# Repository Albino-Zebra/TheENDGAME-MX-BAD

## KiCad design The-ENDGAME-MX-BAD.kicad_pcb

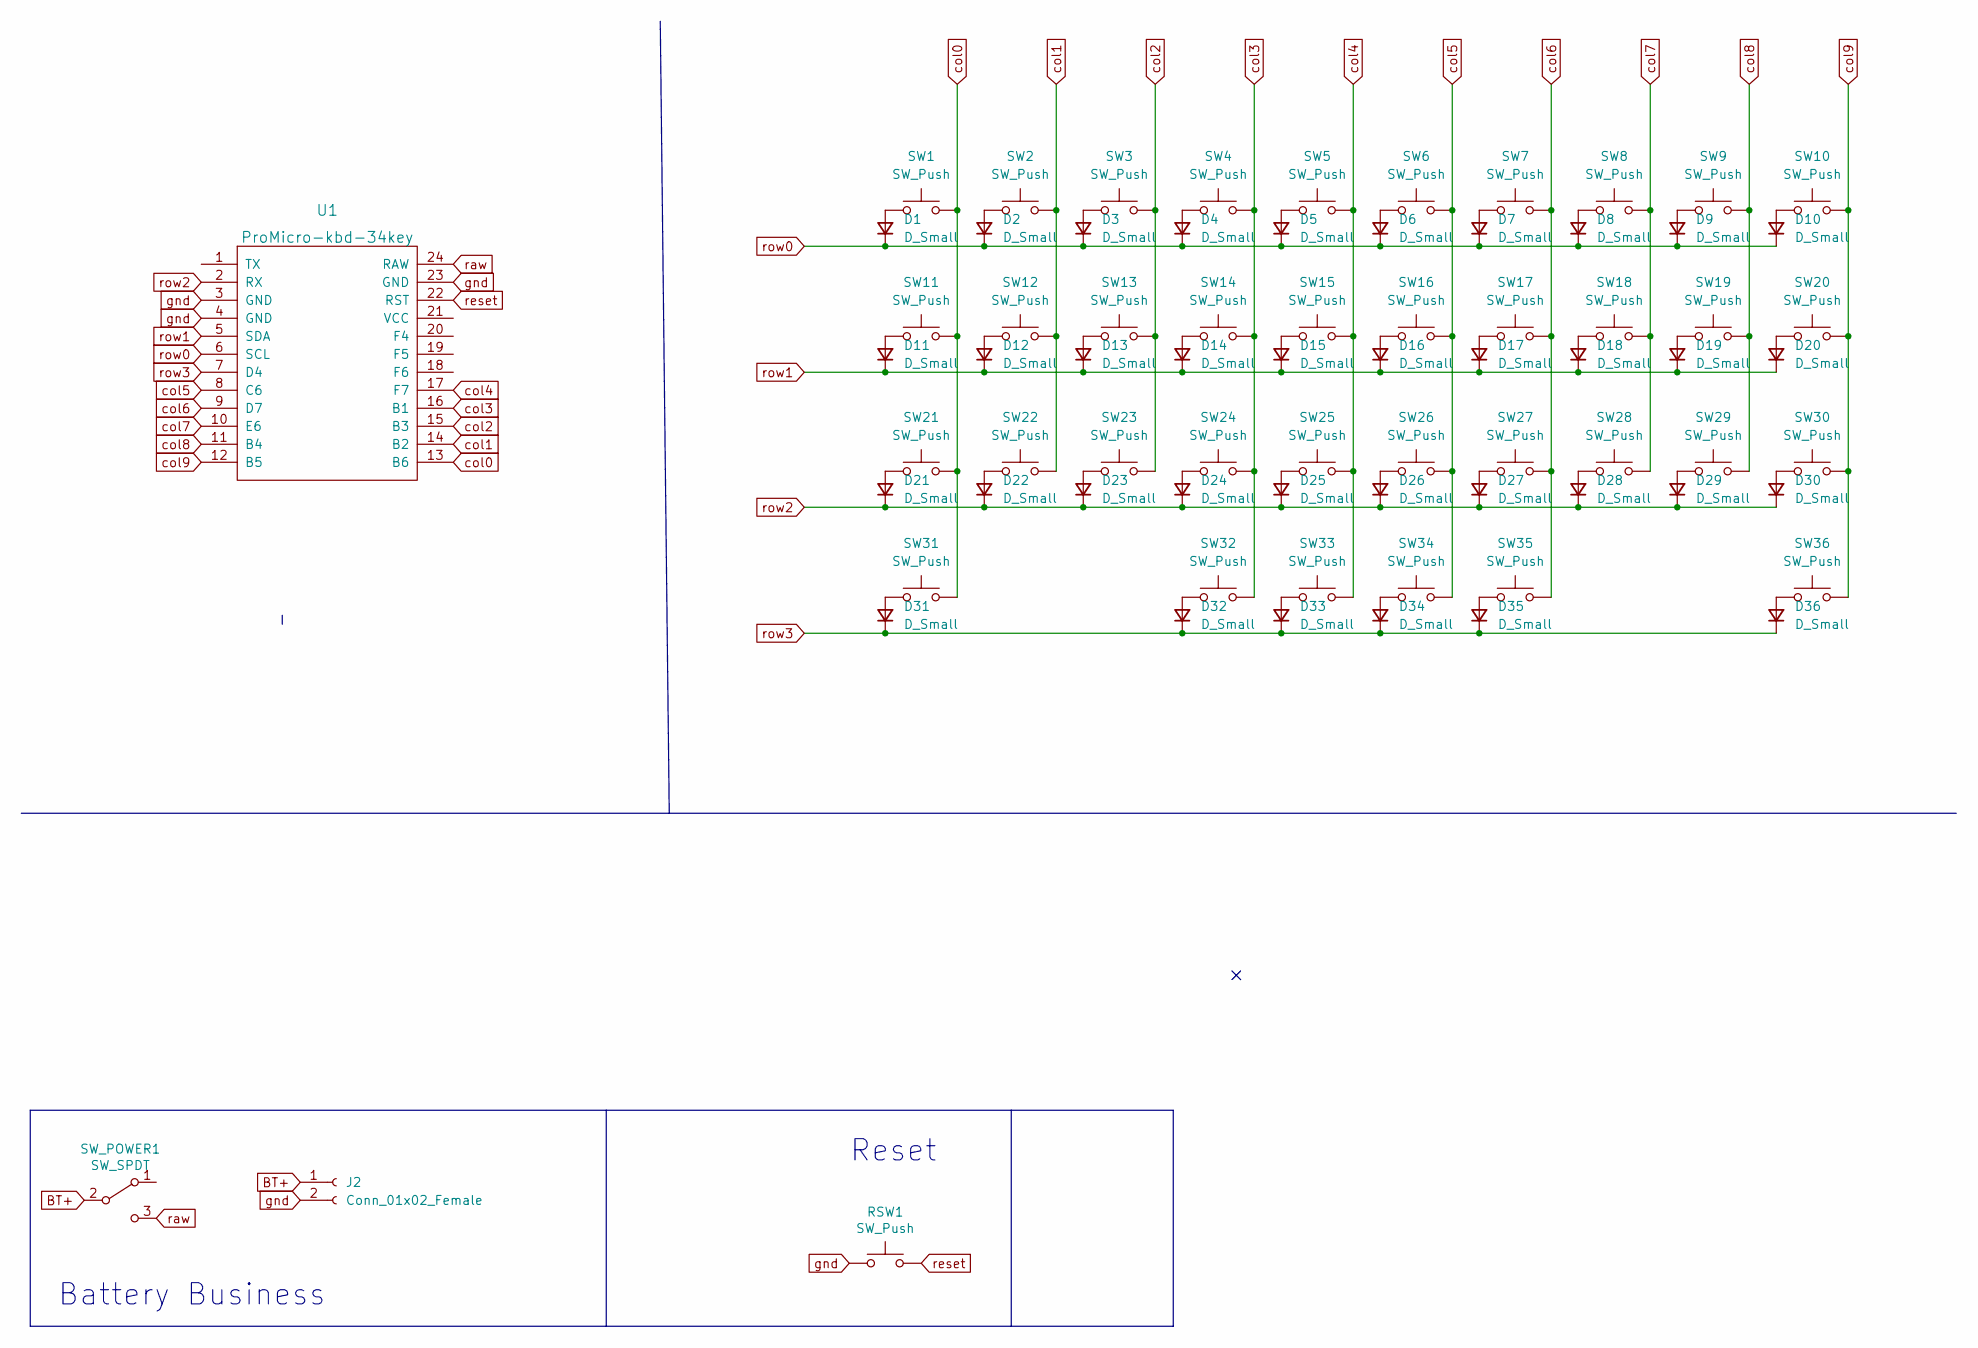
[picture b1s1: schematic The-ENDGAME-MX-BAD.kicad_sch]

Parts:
D1, D2, D3, D4, D5, D6, D7, D8, D9, D10, D11, D12, D13, D14, D15, D16, D17, D18, D19, D20, D21, D22, D23, D24, D25, D26, D27, D28, D29, D30, D31, D32, D33, D34, D35, D36: D_Small
J2: Conn_01x02_Female; JST_PH_S2B-PH-K_1x02_P2.00mm_Horizontal
RSW1: SW_Push; SW_SPST_TL3342
SW1, SW2, SW3, SW4, SW5, SW6, SW7, SW8, SW9, SW10, SW11, SW12, SW13, SW14, SW15, SW16, SW17, SW18, SW19, SW20, SW21, SW22, SW23, SW24, SW25, SW26, SW27, SW28, SW29, SW30, SW31, SW32, SW33, SW34, SW35, SW36: SW_Push; Kailh_socket_PG1350_optional_CLEAN
SW_POWER1: SW_SPDT; SW_SPDT_PCM12
U1: ProMicro-kbd-34key; Elite-C-castellated-24pin-holes

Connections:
BT+: J2.1, SW_POWER1.2 (B)
unnamed: D1.2 (A), SW1.1
unnamed: D2.2 (A), SW2.1
unnamed: D3.2 (A), SW3.1
unnamed: D4.2 (A), SW4.1
unnamed: D5.2 (A), SW5.1
unnamed: D6.2 (A), SW6.1
unnamed: D7.2 (A), SW7.1
unnamed: D8.2 (A), SW8.1
unnamed: D9.2 (A), SW9.1
unnamed: D10.2 (A), SW10.1
unnamed: D11.2 (A), SW11.1
unnamed: D12.2 (A), SW12.1
unnamed: D13.2 (A), SW13.1
unnamed: D14.2 (A), SW14.1
unnamed: D15.2 (A), SW15.1
unnamed: D16.2 (A), SW16.1
unnamed: D17.2 (A), SW17.1
unnamed: D18.2 (A), SW18.1
unnamed: D19.2 (A), SW19.1
unnamed: D20.2 (A), SW20.1
unnamed: D21.2 (A), SW21.1
unnamed: D22.2 (A), SW22.1
unnamed: D23.2 (A), SW23.1
unnamed: D24.2 (A), SW24.1
unnamed: D25.2 (A), SW25.1
unnamed: D26.2 (A), SW26.1
unnamed: D27.2 (A), SW27.1
unnamed: D28.2 (A), SW28.1
unnamed: D29.2 (A), SW29.1
unnamed: D30.2 (A), SW30.1
unnamed: D31.2 (A), SW31.1
unnamed: D32.2 (A), SW32.1
unnamed: D33.2 (A), SW33.1
unnamed: D34.2 (A), SW34.1
unnamed: D35.2 (A), SW35.1
unnamed: D36.2 (A), SW36.1
col0: SW1.2, SW11.2, SW21.2, SW31.2, U1.13 (B6)
col1: SW2.2, SW12.2, SW22.2, U1.14 (B2)
col2: SW3.2, SW13.2, SW23.2, U1.15 (B3)
col3: SW4.2, SW14.2, SW24.2, SW32.2, U1.16 (B1)
col4: SW5.2, SW15.2, SW25.2, SW33.2, U1.17 (F7)
col5: SW6.2, SW16.2, SW26.2, SW34.2, U1.8 (C6)
col6: SW7.2, SW17.2, SW27.2, SW35.2, U1.9 (D7)
col7: SW8.2, SW18.2, SW28.2, U1.10 (E6)
col8: SW9.2, SW19.2, SW29.2, U1.11 (B4)
col9: SW10.2, SW20.2, SW30.2, SW36.2, U1.12 (B5)
gnd: J2.2, RSW1.1, U1.3 (GND), U1.4 (GND), U1.23 (GND)
raw: SW_POWER1.3 (C), U1.24 (RAW)
reset: RSW1.2, U1.22 (RST)
row0: D1.1 (K), D2.1 (K), D3.1 (K), D4.1 (K), D5.1 (K), D6.1 (K), D7.1 (K), D8.1 (K), D9.1 (K), D10.1 (K), U1.6 (SCL)
row1: D11.1 (K), D12.1 (K), D13.1 (K), D14.1 (K), D15.1 (K), D16.1 (K), D17.1 (K), D18.1 (K), D19.1 (K), D20.1 (K), U1.5 (SDA)
row2: D21.1 (K), D22.1 (K), D23.1 (K), D24.1 (K), D25.1 (K), D26.1 (K), D27.1 (K), D28.1 (K), D29.1 (K), D30.1 (K), U1.2 (RX)
row3: D31.1 (K), D32.1 (K), D33.1 (K), D34.1 (K), D35.1 (K), D36.1 (K), U1.7 (D4)

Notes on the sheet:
Reset
Battery Business

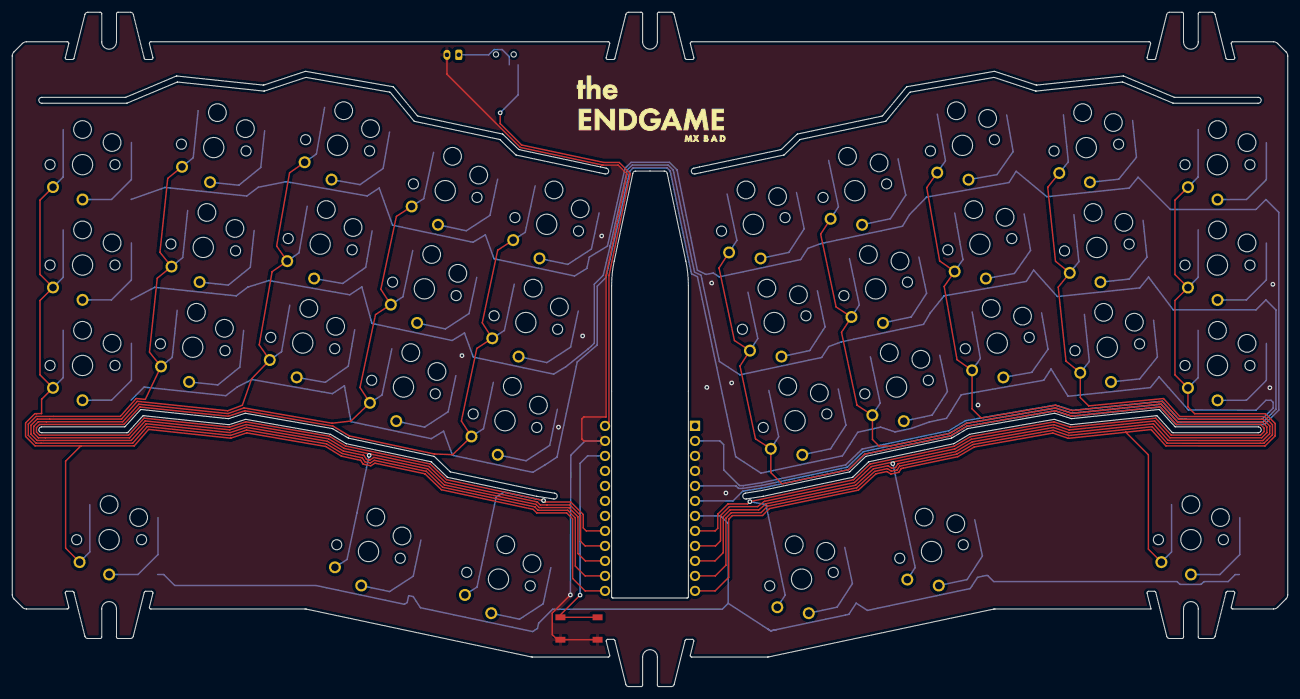
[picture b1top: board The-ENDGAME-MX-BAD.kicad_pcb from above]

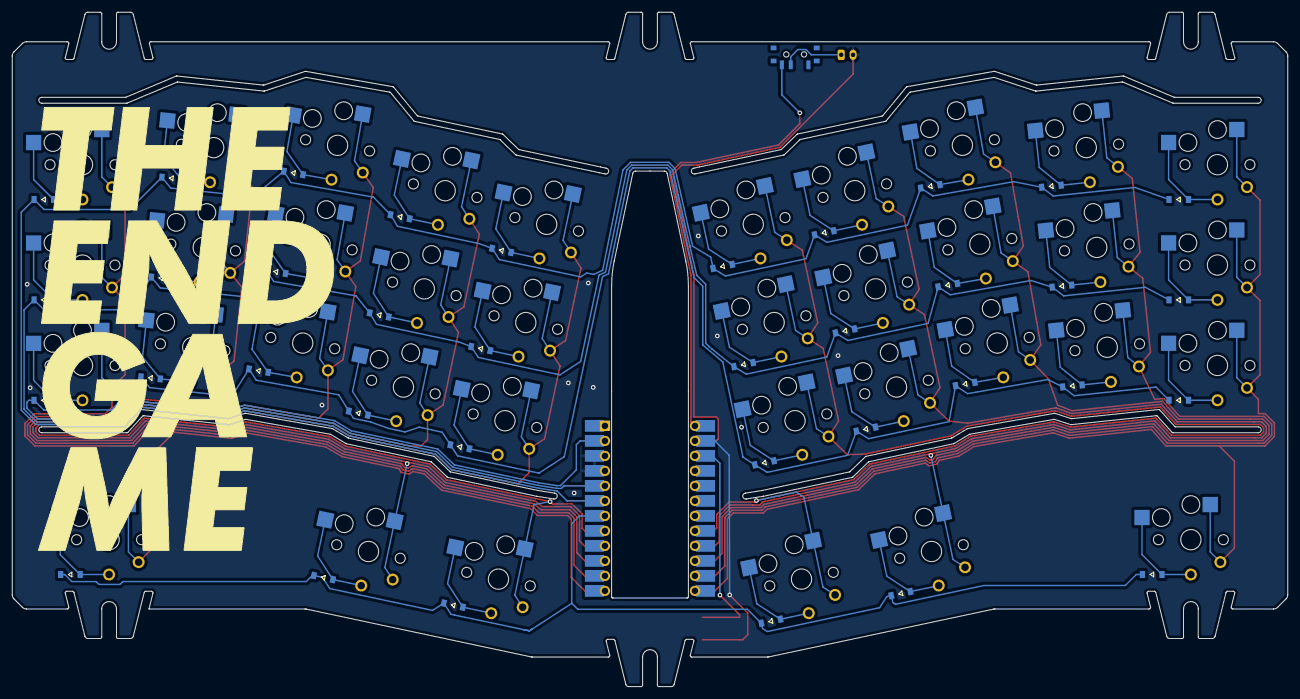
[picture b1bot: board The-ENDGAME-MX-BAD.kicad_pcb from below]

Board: 2 copper layers, 216.0 x 114.2 mm, 76 parts (39 on the bottom side), 54 nets.

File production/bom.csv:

Designator,Footprint,Quantity,Value,LCSC Part #
"D1, D10, D11, D12, D13, D14, D15, D16, D17, D18, D19, D2, D20, D21, D22, D23, D24, D25, D26, D27, D28, D29, D3, D30, D31, D32, D33, D34, D35, D36, D4, D5, D6, D7, D8, D9",D_SOD-123 CLEAN,36,D_Small,
J2,JST_PH_S2B-PH-K_1x02_P2.00mm_Horizontal,1,Conn_01x02_Female,
RSW1,SW_SPST_TL3342,1,SW_Push,
"SW1, SW10, SW11, SW12, SW13, SW14, SW15, SW16, SW17, SW18, SW19, SW2, SW20, SW21, SW22, SW23, SW24, SW25, SW26, SW27, SW28, SW29, SW3, SW30, SW31, SW32, SW33, SW34, SW35, SW36, SW4, SW5, SW6, SW7, SW8, SW9",Kailh_socket_PG1350_optional_CLEAN,36,SW_Push,
SW_POWER1,SW_SPDT_PCM12,1,SW_SPDT,
U1,Elite-C-castellated-24pin-holes,1,ProMicro-kbd-34key,

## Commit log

2022-09-29 unnützer stuff gelöscht
2022-09-29 noch mehr nutzloser stuff gelöscht
2022-09-29 fast fertig
2022-10-11 pcb changes
2022-10-15 soweit so gut ENDGAME outline und layout final
2022-10-16 backup cause things can happen
2022-10-18 updates updates upddfkjds
2022-10-19 ja ja push den scheis
2022-10-19 back das up baby
2022-10-24 biba backup
2022-11-04 backup gibts ja auch noch
2022-12-08 now or never
2022-12-18 diode pads bigger
